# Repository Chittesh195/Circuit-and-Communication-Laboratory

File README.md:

# 📐 Triangular Wave Generator Using Op-Amp (LM741)

### 🔧 23ECE286 – Circuits and Communication Lab Term Project  

---

## 📘 Project Overview

This project focuses on the **design, simulation, and hardware implementation** of a **triangular wave generator** using **operational amplifiers (LM741)**. The waveform's frequency is **adjustable between 250 Hz and 2.5 kHz**, making it suitable for various signal processing and waveform synthesis applications.

---

## 🎯 Objectives

- Design a **Schmitt Trigger** using LM741 to generate a square wave.
- Build an **Integrator** circuit to convert the square wave into a triangular waveform.
- Achieve a **variable frequency range of 250 Hz to 2.5 kHz**.
- Simulate the circuit using **LTSpice**.
- Implement and test the circuit using **hardware and oscilloscope measurements**.
- Analyze waveform quality and component impact.

---

## 🛠️ Circuit Description

The circuit consists of two main stages:

1. **Schmitt Trigger (Comparator)**
   - Uses LM741 with positive feedback to generate a square wave.
   - Switching thresholds set via voltage divider network.

2. **Integrator**
   - Converts the square wave into a triangular wave.
   - Built with LM741, resistors, and capacitors.

---

## ⚙️ Key Components

| Component           | Specification             |
|---------------------|---------------------------|
| Op-Amp              | LM741 × 2                 |
| Potentiometer       | 4.7 kΩ to 470 kΩ (variable resistor) |
| Resistors           | 1 kΩ, 4.7 kΩ, 12 kΩ        |
| Capacitor           | 0.1 µF                    |
| Power Supply        | ±12 V                     |
| Oscilloscope        | For waveform observation  |
| Breadboard & Wires  | For hardware setup        |

---

## 🔢 Frequency Calculations

Formula used:
```
f = R1 / (4 × R × C × R2)
```

- For **250 Hz**: R = 47 kΩ  
- For **2.5 kHz**: R = 4.7 kΩ  

---

## 🧪 Simulation & Implementation

- **LTSpice** used for waveform validation.
- Hardware circuit implemented on **breadboard**.
- **Oscilloscope** verified clean triangular wave output.
- Adjusting the potentiometer varied the frequency across the desired range.

---

## 📈 Results

- **Waveform Quality**: Stable triangular waveform across entire frequency range.
- **Frequency Range Achieved**: 250 Hz to 2.5 kHz.
- **Simulation and experimental results** closely matched.

| Potentiometer (R) | Frequency (Approx.) |
|-------------------|----------------------|
| 47 kΩ             | 250 Hz               |
| 4.7 kΩ            | 2.5 kHz              |

---

## ⚠️ Challenges & Solutions

| Challenge                    | Solution                                |
|-----------------------------|-----------------------------------------|
| Resistor value mismatches   | Used nearest standard values and recalculated |
| Frequency drift             | Used precision 1% tolerance components  |
| Op-amp limitations          | Optimized for LM741’s bandwidth         |

---

## 📌 Applications

- Signal and function generators  
- Audio waveform synthesis  
- Communication systems (modulation/wave shaping)  

---

## 📚 References

1. Sedra A., Smith K. C., *Microelectronic Circuits*, 6th ed., Oxford University Press, 2010.  
2. Texas Instruments, *Designing With Operational Amplifiers*, [TI Report](https://www.ti.com/lit/pdf/tidu020)

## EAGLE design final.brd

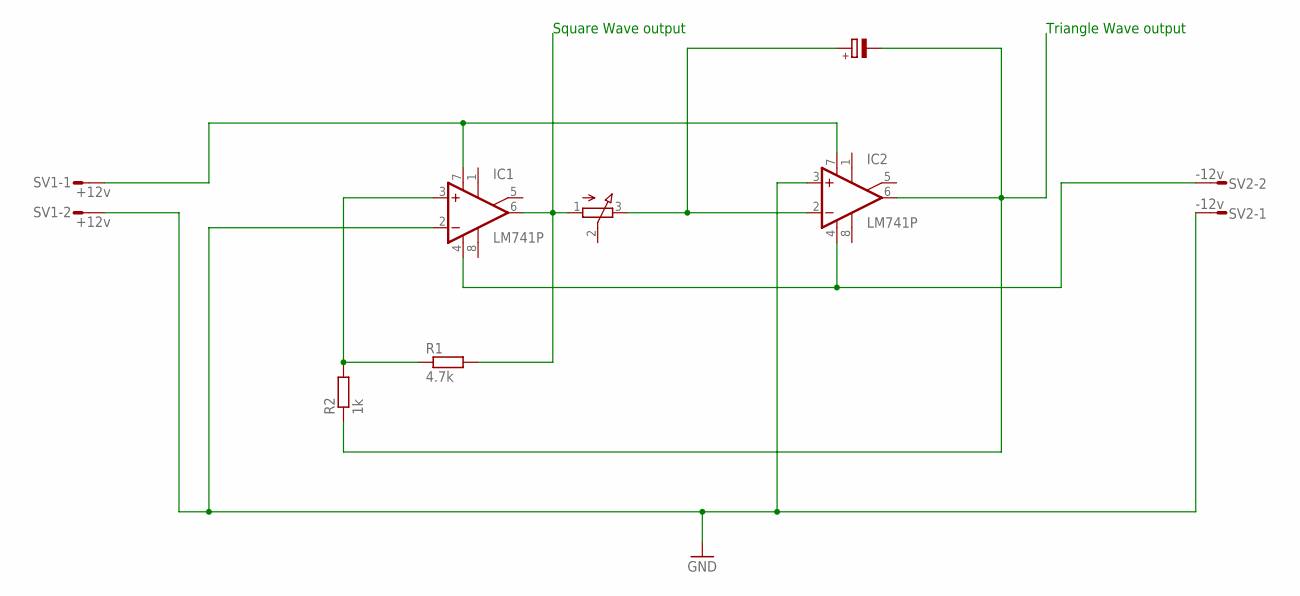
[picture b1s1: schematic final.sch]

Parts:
C1: 0.1u; E5-6
IC1, IC2: LM741P; DIL08
P1: 4.7k--47k; 3RP/1610N
R1: 4.7k; P0613/15
R2: 1k; P0613/15
SV1: +12v; L02P
SV2: -12v; L02P

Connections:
GND: IC1.2 (-IN), IC2.3 (+IN), SV1.2, SV2.1
unnamed: IC1.7 (V+), IC2.7 (V+), SV1.1
unnamed: C1.+, IC2.2 (-IN), P1.3 (E)
unnamed: C1.-, IC2.6 (OUT), R2.1
unnamed: IC1.3 (+IN), R1.1, R2.2
unnamed: IC1.6 (OUT), P1.1 (A), R1.2
unnamed: IC1.4 (V-), IC2.4 (V-), SV2.2

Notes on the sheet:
Square Wave output
Triangle Wave output

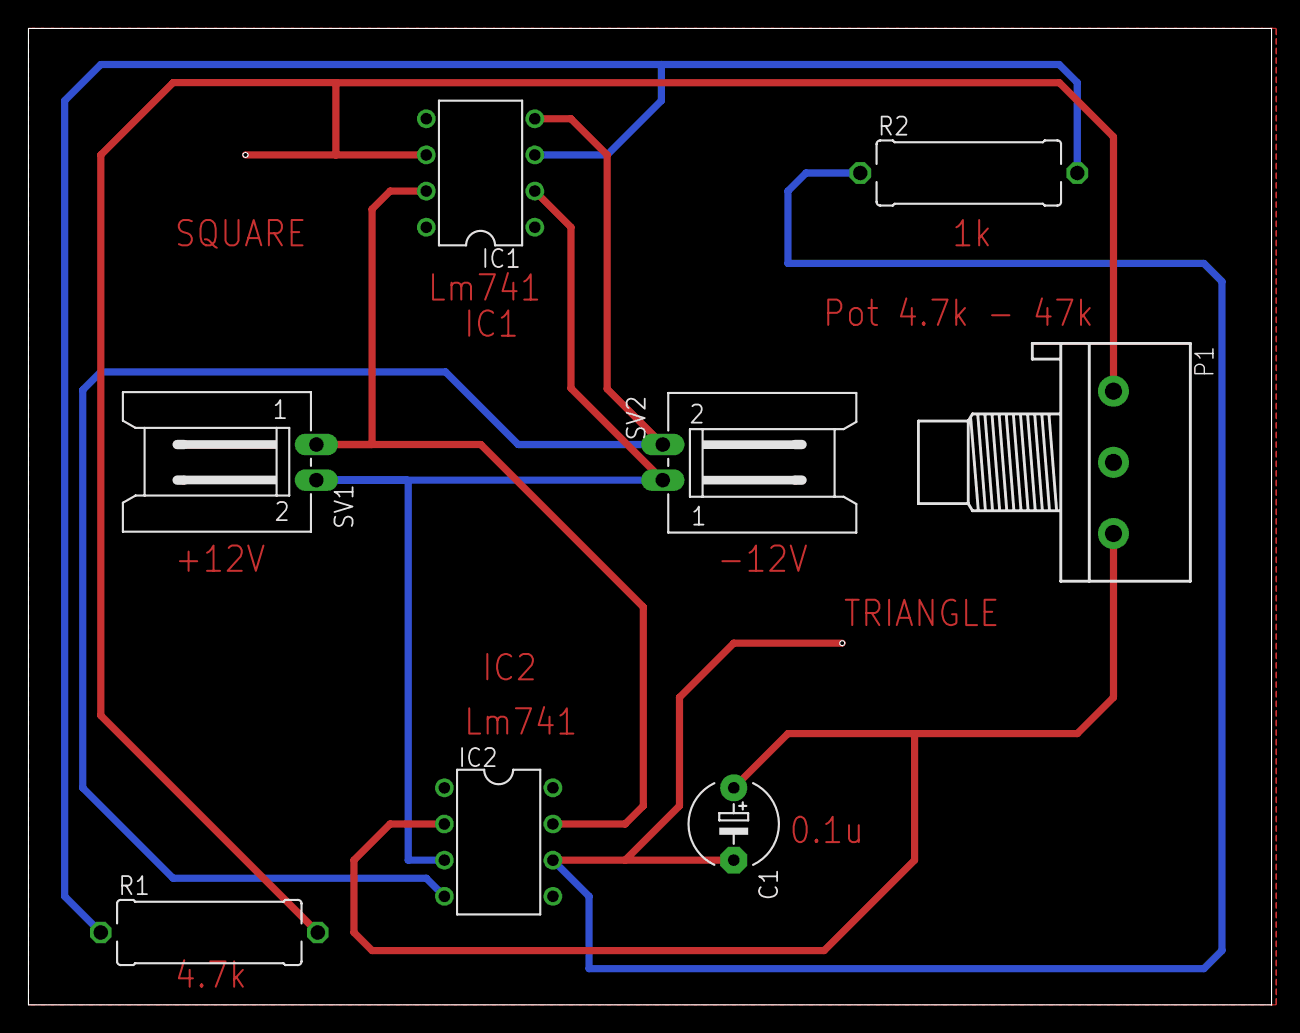
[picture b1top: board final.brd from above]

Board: 2 copper layers, 87.3 x 68.6 mm, 8 parts (0 on the bottom side), 7 nets.
